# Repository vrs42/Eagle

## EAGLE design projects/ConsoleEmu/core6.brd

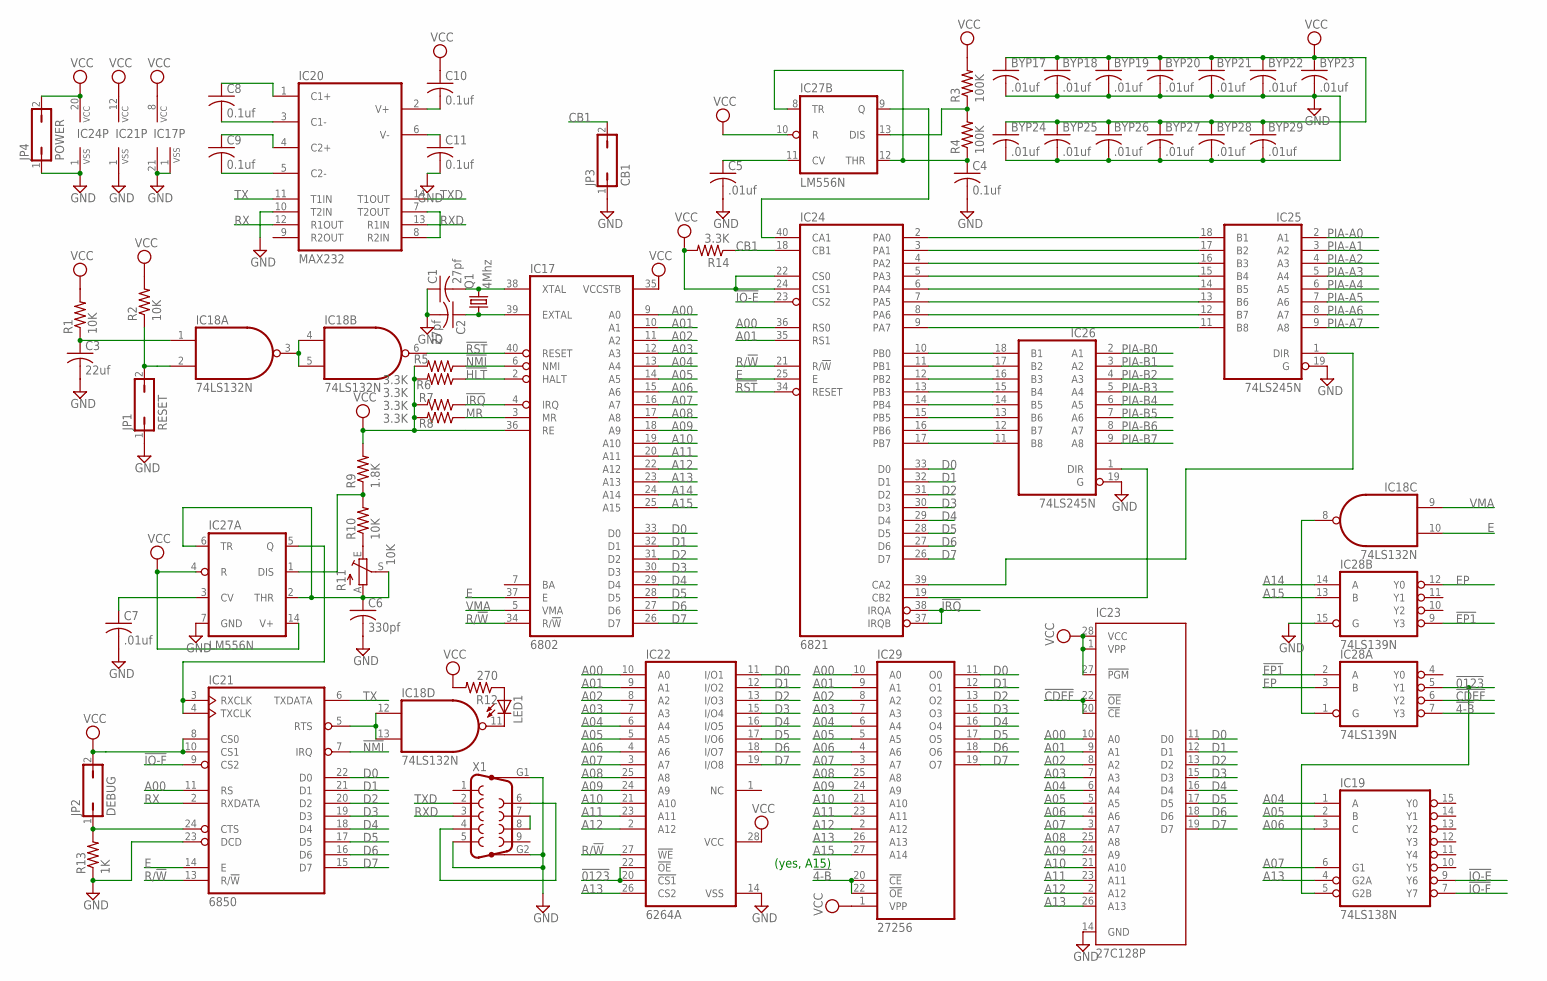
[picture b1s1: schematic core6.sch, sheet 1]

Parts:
BYP17, BYP18, BYP19, BYP20, BYP21, BYP22, BYP23, BYP24, BYP25, BYP26, BYP27, BYP28, BYP29: .01uf; C050-025X075
C1, C2: 27pf; C050-025X075
C3: 22uf; C102-043X133
C4, C8, C9, C10, C11: 0.1uf; C050-025X075
C5, C7: .01uf; C050-025X075
C6: 330pf; C050-025X075
IC17: 6802; DIL40
IC18: 74LS132N; DIL14
IC19: 74LS138N; DIL16
IC20: MAX232; DIL16
IC21: 6850; DIL24
IC22: 6264A; DIL28-6
IC23: 27C128P; DIL28-6
IC24: 6821; DIL40
IC25, IC26: 74LS245N; DIL20
IC27: LM556N; DIL14
IC28: 74LS139N; DIL16
IC29: 27256; DIL28
JP1: RESET; JP1
JP2: DEBUG; JP1
JP3: CB1; JP1
JP4: POWER; JP1
LED1: LED3MM
Q1: 4Mhz; HC18U-V
R1, R2, R10: 10K; 0207/7
R3, R4: 100K; 0207/7
R5, R6, R7, R8, R14: 3.3K; 0207/7
R9: 1.8K; 0207/7
R11: 10K; SP19L
R12: 270; 0207/7
R13: 1K; 0207/7
X1: F09HP

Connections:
!4-B: IC28.7 (Y3), IC29.20 (!CE), IC29.22 (!OE)
!0123: IC19.5 (G2B), IC22.20 (!CS1), IC22.22 (!OE), IC28.5 (Y1)
!CDEF: IC23.20 (!CE), IC23.22 (!OE), IC28.6 (Y2)
!EP1: IC28.2 (A), IC28.9 (Y3)
!HLT: IC17.2 (HALT), R5.1
!IO-E: IC19.9 (Y6), IC24.23 (CS2)
!IO-F: IC19.7 (Y7), IC21.9 (CS2)
!IRQ: IC17.4 (IRQ), IC24.37 (IRQB), IC24.38 (IRQA), R7.1
!NMI: IC17.6 (NMI), IC21.7 (IRQ), R6.1
!RST: IC17.40 (RESET), IC18.6 (O), IC24.34 (RESET)
A00: IC17.9 (A0), IC21.11 (RS), IC22.10 (A0), IC23.10 (A0), IC24.36 (RS0), IC29.10 (A0)
A01: IC17.10 (A1), IC22.9 (A1), IC23.9 (A1), IC24.35 (RS1), IC29.9 (A1)
A02: IC17.11 (A2), IC22.8 (A2), IC23.8 (A2), IC29.8 (A2)
A03: IC17.12 (A3), IC22.7 (A3), IC23.7 (A3), IC29.7 (A3)
A04: IC17.13 (A4), IC19.1 (A), IC22.6 (A4), IC23.6 (A4), IC29.6 (A4)
A05: IC17.14 (A5), IC19.2 (B), IC22.5 (A5), IC23.5 (A5), IC29.5 (A5)
A06: IC17.15 (A6), IC19.3 (C), IC22.4 (A6), IC23.4 (A6), IC29.4 (A6)
A07: IC17.16 (A7), IC19.6 (G1), IC22.3 (A7), IC23.3 (A7), IC29.3 (A7)
A08: IC17.17 (A8), IC22.25 (A8), IC23.25 (A8), IC29.25 (A8)
A09: IC17.18 (A9), IC22.24 (A9), IC23.24 (A9), IC29.24 (A9)
A10: IC17.19 (A10), IC22.21 (A10), IC23.21 (A10), IC29.21 (A10)
A11: IC17.20 (A11), IC22.23 (A11), IC23.23 (A11), IC29.23 (A11)
A12: IC17.22 (A12), IC22.2 (A12), IC23.2 (A12), IC29.2 (A12)
A13: IC17.23 (A13), IC19.4 (G2A), IC22.26 (CS2), IC23.26 (A13), IC29.26 (A13)
A14: IC17.24 (A14), IC28.14 (A)
A15: IC17.25 (A15), IC28.13 (B), IC29.27 (A14)
CB1: IC24.18 (CB1), JP3.2, R14.1
D0: IC17.33 (D0), IC21.22 (D0), IC22.11 (I/O1), IC23.11 (D0), IC24.33 (D0), IC29.11 (O0)
D1: IC17.32 (D1), IC21.21 (D1), IC22.12 (I/O2), IC23.12 (D1), IC24.32 (D1), IC29.12 (O1)
D2: IC17.31 (D2), IC21.20 (D2), IC22.13 (I/O3), IC23.13 (D2), IC24.31 (D2), IC29.13 (O2)
D3: IC17.30 (D3), IC21.19 (D3), IC22.15 (I/O4), IC23.15 (D3), IC24.30 (D3), IC29.15 (O3)
D4: IC17.29 (D4), IC21.18 (D4), IC22.16 (I/O5), IC23.16 (D4), IC24.29 (D4), IC29.16 (O4)
D5: IC17.28 (D5), IC21.17 (D5), IC22.17 (I/O6), IC23.17 (D5), IC24.28 (D5), IC29.17 (O5)
D6: IC17.27 (D6), IC21.16 (D6), IC22.18 (I/O7), IC23.18 (D6), IC24.27 (D6), IC29.18 (O6)
D7: IC17.26 (D7), IC21.15 (D7), IC22.19 (I/O8), IC23.19 (D7), IC24.26 (D7), IC29.19 (O7)
E: IC17.37 (E), IC18.10 (I1), IC21.14 (E), IC24.25 (E)
EP: IC28.3 (B), IC28.12 (Y0)
GND: BYP17.2, BYP18.2, BYP19.2, BYP20.2, BYP21.2, BYP22.2, BYP23.2, BYP24.2, BYP25.2, BYP26.2, BYP27.2, BYP28.2, BYP29.2, C1.1, C2.2, C3.2, C4.2, C5.2, C6.2, C7.2, C11.2, IC17.1 (VSS), IC17.21 (VSS), IC18.7 (GND), IC19.8 (GND), IC20.10 (T2IN), IC20.15 (GND), IC21.1 (VSS), IC21.23 (DCD), IC22.14 (VSS), IC23.14 (GND), IC24.1 (VSS), IC25.10 (GND), IC25.19 (G), IC26.10 (GND), IC26.19 (G), IC27.7 (GND), IC28.8 (GND), IC28.15 (G), IC29.14 (GND), JP1.1, JP3.1, JP4.1, R13.1, X1.5, X1.G1, X1.G2; also elsewhere on the board
MR: IC17.3 (MR), R8.1
unnamed: C2.1, IC17.39 (EXTAL), Q1.1
unnamed: C1.2, IC17.38 (XTAL), Q1.2
unnamed: IC24.2 (PA0), IC25.18 (B1)
unnamed: IC18.3 (O), IC18.4 (I0), IC18.5 (I1)
unnamed: C3.1, IC18.1 (I0), R1.1
unnamed: IC18.2 (I1), JP1.2, R2.1
unnamed: IC21.3 (RXCLK), IC21.4 (TXCLK), IC27.5 (Q)
unnamed: IC24.10 (PB0), IC26.18 (B1)
unnamed: IC24.11 (PB1), IC26.17 (B2)
unnamed: C6.1, IC27.2 (THR), IC27.6 (TR), R11.A, R11.S
unnamed: IC27.1 (DIS), R9.1, R10.2
unnamed: IC24.12 (PB2), IC26.16 (B3)
unnamed: IC24.13 (PB3), IC26.15 (B4)
unnamed: IC24.14 (PB4), IC26.14 (B5)
unnamed: IC24.15 (PB5), IC26.13 (B6)
unnamed: IC24.16 (PB6), IC26.12 (B7)
unnamed: IC24.17 (PB7), IC26.11 (B8)
unnamed: IC24.3 (PA1), IC25.17 (B2)
unnamed: IC24.4 (PA2), IC25.16 (B3)
unnamed: IC24.5 (PA3), IC25.15 (B4)
unnamed: IC24.6 (PA4), IC25.14 (B5)
unnamed: IC24.7 (PA5), IC25.13 (B6)
unnamed: IC24.8 (PA6), IC25.12 (B7)
unnamed: IC24.9 (PA7), IC25.11 (B8)
unnamed: IC24.19 (CB2), IC26.1 (DIR)
unnamed: IC24.39 (CA2), IC25.1 (DIR)
unnamed: IC24.40 (CA1), IC27.9 (Q)
unnamed: C4.1, IC27.8 (TR), IC27.12 (THR), R4.1
unnamed: IC27.13 (DIS), R3.1, R4.2
unnamed: C5.1, IC27.11 (CV)
unnamed: R10.1, R11.E
unnamed: X1.4, X1.6
unnamed: X1.7, X1.8
unnamed: IC18.12 (I0), IC18.13 (I1), IC21.5 (RTS)
unnamed: IC18.11 (O), LED1.K (C)
unnamed: LED1.A, R12.1
unnamed: IC21.24 (CTS), JP2.1, R13.2
unnamed: IC18.8 (O), IC28.1 (G)
unnamed: IC20.7 (T2OUT), IC20.8 (R2IN)
unnamed: C7.1, IC27.3 (CV)
unnamed: C9.2, IC20.5 (C2-)
unnamed: C9.1, IC20.4 (C2+)
unnamed: C8.2, IC20.3 (C1-)
unnamed: C8.1, IC20.1 (C1+)
unnamed: C11.1, IC20.6 (V-)
unnamed: C10.2, IC20.2 (V+)
PIA-A0: IC25.2 (A1); also elsewhere on the board
PIA-A1: IC25.3 (A2); also elsewhere on the board
PIA-A2: IC25.4 (A3); also elsewhere on the board
PIA-A3: IC25.5 (A4); also elsewhere on the board
PIA-A4: IC25.6 (A5); also elsewhere on the board
PIA-A5: IC25.7 (A6); also elsewhere on the board
PIA-A6: IC25.8 (A7); also elsewhere on the board
PIA-A7: IC25.9 (A8); also elsewhere on the board
PIA-B0: IC26.2 (A1); also elsewhere on the board
PIA-B1: IC26.3 (A2); also elsewhere on the board
PIA-B2: IC26.4 (A3); also elsewhere on the board
PIA-B3: IC26.5 (A4); also elsewhere on the board
PIA-B4: IC26.6 (A5); also elsewhere on the board
PIA-B5: IC26.7 (A6); also elsewhere on the board
PIA-B6: IC26.8 (A7); also elsewhere on the board
PIA-B7: IC26.9 (A8); also elsewhere on the board
R/!W: IC17.34 (R/!W), IC21.13 (R/!W), IC22.27 (!WE), IC24.21 (R/!W)
RX: IC20.12 (R1OUT), IC21.2 (RXDATA)
RXD: IC20.13 (R1IN), X1.3
TX: IC20.11 (T1IN), IC21.6 (TXDATA)
TXD: IC20.14 (T1OUT), X1.2
VCC: BYP17.1, BYP18.1, BYP19.1, BYP20.1, BYP21.1, BYP22.1, BYP23.1, BYP24.1, BYP25.1, BYP26.1, BYP27.1, BYP28.1, BYP29.1, C10.1, IC17.8 (VCC), IC17.35 (VCCSTB), IC17.36 (RE), IC18.14 (VCC), IC19.16 (VCC), IC20.16 (VCC), IC21.8 (CS0), IC21.10 (CS1), IC21.12 (VCC), IC22.28 (VCC), IC23.1 (VPP), IC23.27 (!PGM), IC23.28 (VCC), IC24.20 (VCC), IC24.22 (CS0), IC24.24 (CS1), IC25.20 (VCC), IC26.20 (VCC), IC27.4 (R), IC27.10 (R), IC27.14 (V+), IC28.16 (VCC), IC29.1 (VPP), IC29.28 (VCC), JP2.2, JP4.2, R1.2, R2.2, R3.2, R5.2, R6.2, R7.2, R8.2, R9.2, R12.2, R14.2; also elsewhere on the board
VMA: IC17.5 (VMA), IC18.9 (I0)

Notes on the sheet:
(yes, A15)

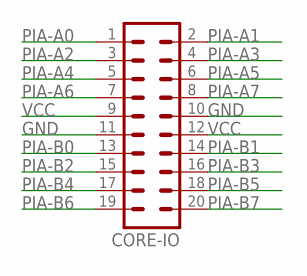
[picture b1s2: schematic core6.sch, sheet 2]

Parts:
CORE-IO: MA10-2

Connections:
GND: CORE-IO.10, CORE-IO.11; also elsewhere on the board
PIA-A0: CORE-IO.1; also elsewhere on the board
PIA-A1: CORE-IO.2; also elsewhere on the board
PIA-A2: CORE-IO.3; also elsewhere on the board
PIA-A3: CORE-IO.4; also elsewhere on the board
PIA-A4: CORE-IO.5; also elsewhere on the board
PIA-A5: CORE-IO.6; also elsewhere on the board
PIA-A6: CORE-IO.7; also elsewhere on the board
PIA-A7: CORE-IO.8; also elsewhere on the board
PIA-B0: CORE-IO.13; also elsewhere on the board
PIA-B1: CORE-IO.14; also elsewhere on the board
PIA-B2: CORE-IO.15; also elsewhere on the board
PIA-B3: CORE-IO.16; also elsewhere on the board
PIA-B4: CORE-IO.17; also elsewhere on the board
PIA-B5: CORE-IO.18; also elsewhere on the board
PIA-B6: CORE-IO.19; also elsewhere on the board
PIA-B7: CORE-IO.20; also elsewhere on the board
VCC: CORE-IO.9, CORE-IO.12; also elsewhere on the board

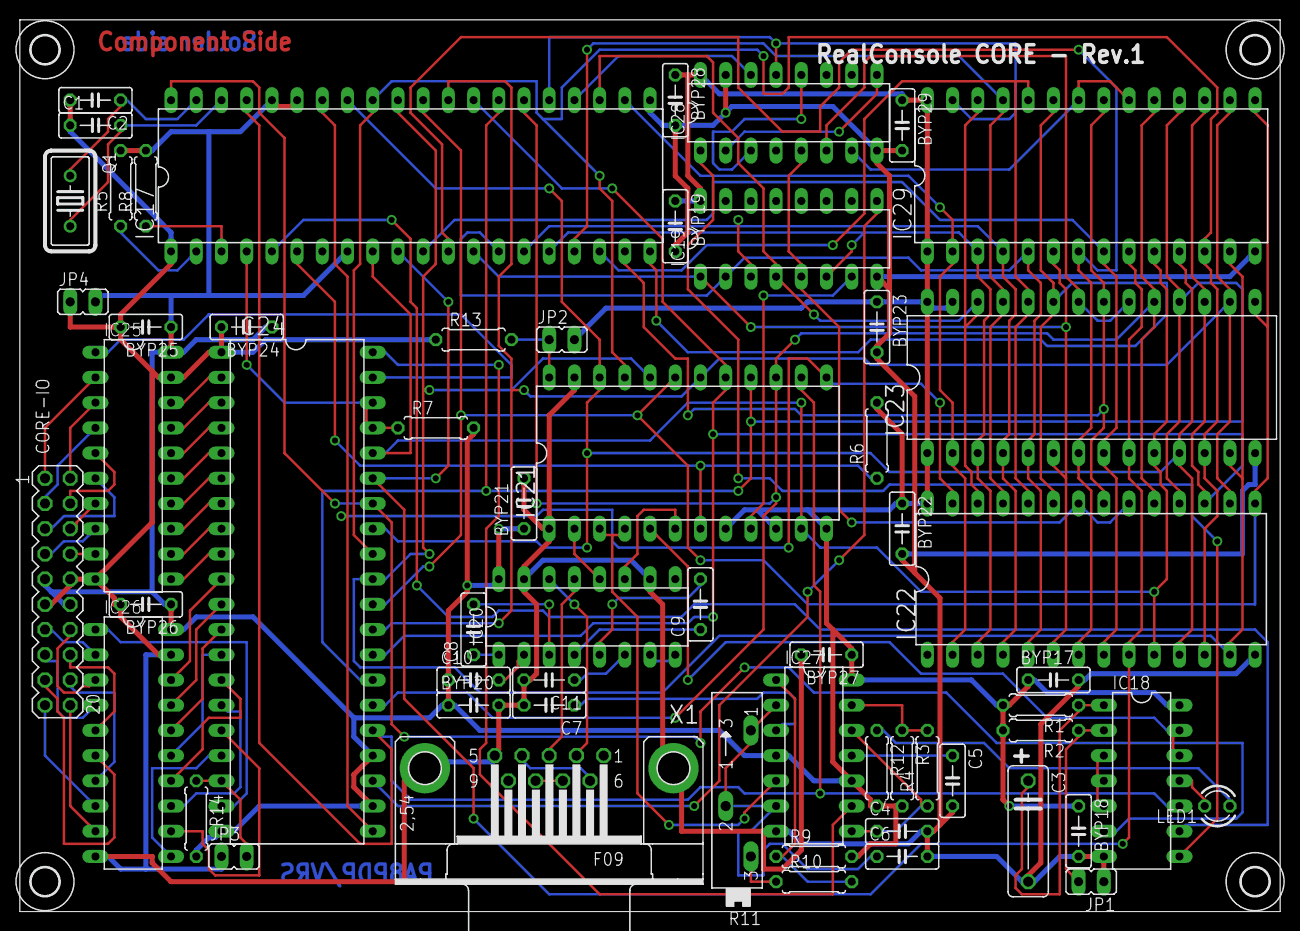
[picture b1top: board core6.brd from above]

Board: 2 copper layers, 127.0 x 89.8 mm, 63 parts (0 on the bottom side), 108 nets.

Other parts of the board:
U$3, U$4, U$5, U$6: 2,8

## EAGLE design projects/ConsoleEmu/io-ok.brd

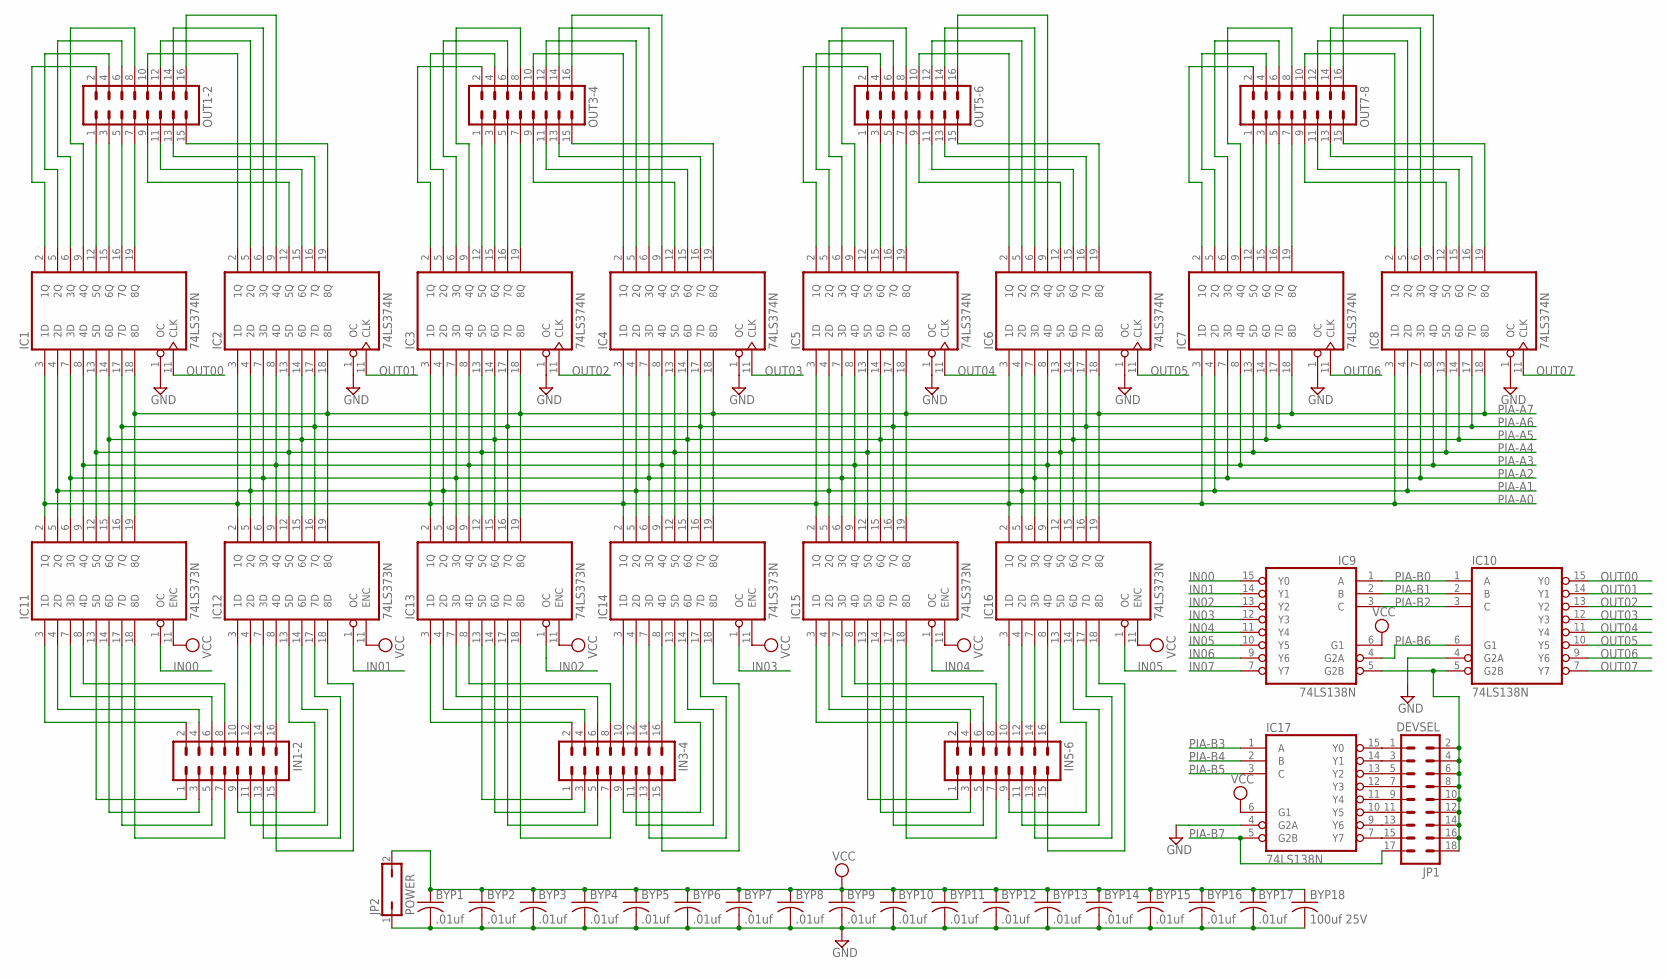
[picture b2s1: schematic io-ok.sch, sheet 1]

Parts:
BYP1, BYP2, BYP3, BYP4, BYP5, BYP6, BYP7, BYP8, BYP9, BYP10, BYP11, BYP12, BYP13, BYP14, BYP15, BYP16, BYP17: .01uf; C050-025X075
BYP18: 100uf 25V; C150-064X183
IC1, IC2, IC3, IC4, IC5, IC6, IC7, IC8: 74LS374N; DIL20
IC9, IC10, IC17: 74LS138N; DIL16
IC11, IC12, IC13, IC14, IC15, IC16: 74LS373N; DIL20
IN1-2, IN3-4, IN5-6: MA08-2
JP1: DEVSEL; MA09-2
JP2: POWER; JP1
OUT1-2, OUT3-4, OUT5-6, OUT7-8: MA08-2

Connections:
GND: BYP1.2, BYP2.2, BYP3.2, BYP4.2, BYP5.2, BYP6.2, BYP7.2, BYP8.2, BYP9.2, BYP10.2, BYP11.2, BYP12.2, BYP13.2, BYP14.2, BYP15.2, BYP16.2, BYP17.2, BYP18.2, IC1.1 (OC), IC1.10 (GND), IC2.1 (OC), IC2.10 (GND), IC3.1 (OC), IC3.10 (GND), IC4.1 (OC), IC4.10 (GND), IC5.1 (OC), IC5.10 (GND), IC6.1 (OC), IC6.10 (GND), IC7.1 (OC), IC7.10 (GND), IC8.1 (OC), IC8.10 (GND), IC9.8 (GND), IC10.4 (G2A), IC10.8 (GND), IC11.10 (GND), IC12.10 (GND), IC13.10 (GND), IC14.10 (GND), IC15.10 (GND), IC16.10 (GND), IC17.4 (G2A), IC17.8 (GND), JP2.1; also elsewhere on the board
IN00: IC9.15 (Y0), IC11.1 (OC)
IN01: IC9.14 (Y1), IC12.1 (OC)
IN02: IC9.13 (Y2), IC13.1 (OC)
IN03: IC9.12 (Y3), IC14.1 (OC)
IN04: IC9.11 (Y4), IC15.1 (OC)
IN05: IC9.10 (Y5), IC16.1 (OC)
IN06: IC9.9 (Y6)
IN07: IC9.7 (Y7)
unnamed: IC12.3 (1D), IN1-2.10
unnamed: IC12.4 (2D), IN1-2.12
unnamed: IC17.15 (Y0), JP1.1
unnamed: IC17.14 (Y1), JP1.3
unnamed: IC17.13 (Y2), JP1.5
unnamed: IC17.12 (Y3), JP1.7
unnamed: IC12.7 (3D), IN1-2.14
unnamed: IC12.8 (4D), IN1-2.16
unnamed: IC11.8 (4D), IN1-2.8
unnamed: IC11.7 (3D), IN1-2.6
unnamed: IC11.4 (2D), IN1-2.4
unnamed: IC11.3 (1D), IN1-2.2
unnamed: IC11.13 (5D), IN1-2.1
unnamed: IC11.14 (6D), IN1-2.3
unnamed: IC11.17 (7D), IN1-2.5
unnamed: IC11.18 (8D), IN1-2.7
unnamed: IC12.13 (5D), IN1-2.9
unnamed: IC12.14 (6D), IN1-2.11
unnamed: IC12.17 (7D), IN1-2.13
unnamed: IC12.18 (8D), IN1-2.15
unnamed: IC17.11 (Y4), JP1.9
unnamed: IC17.10 (Y5), JP1.11
unnamed: IC17.9 (Y6), JP1.13
unnamed: IC17.7 (Y7), JP1.15
unnamed: IC9.5 (G2B), IC10.5 (G2B), JP1.2, JP1.4, JP1.6, JP1.8, JP1.10, JP1.12, JP1.14, JP1.16, JP1.18
unnamed: IC5.2 (1Q), OUT5-6.2
unnamed: IC7.2 (1Q), OUT7-8.2
unnamed: IC14.3 (1D), IN3-4.10
unnamed: IC14.4 (2D), IN3-4.12
unnamed: IC14.7 (3D), IN3-4.14
unnamed: IC14.8 (4D), IN3-4.16
unnamed: IC3.12 (5Q), OUT3-4.1
unnamed: IC3.15 (6Q), OUT3-4.3
unnamed: IC3.16 (7Q), OUT3-4.5
unnamed: IC3.19 (8Q), OUT3-4.7
unnamed: IC13.3 (1D), IN3-4.2
unnamed: IC13.4 (2D), IN3-4.4
unnamed: IC13.7 (3D), IN3-4.6
unnamed: IC13.8 (4D), IN3-4.8
unnamed: IC14.13 (5D), IN3-4.9
unnamed: IC14.14 (6D), IN3-4.11
unnamed: IC14.17 (7D), IN3-4.13
unnamed: IC14.18 (8D), IN3-4.15
unnamed: IC13.13 (5D), IN3-4.1
unnamed: IC13.14 (6D), IN3-4.3
unnamed: IC13.17 (7D), IN3-4.5
unnamed: IC13.18 (8D), IN3-4.7
unnamed: IC3.5 (2Q), OUT3-4.4
unnamed: IC3.6 (3Q), OUT3-4.6
unnamed: IC3.2 (1Q), OUT3-4.2
unnamed: IC3.9 (4Q), OUT3-4.8
unnamed: IC1.12 (5Q), OUT1-2.1
unnamed: IC1.15 (6Q), OUT1-2.3
unnamed: IC1.16 (7Q), OUT1-2.5
unnamed: IC1.19 (8Q), OUT1-2.7
unnamed: IC1.2 (1Q), OUT1-2.2
unnamed: IC1.5 (2Q), OUT1-2.4
unnamed: IC1.6 (3Q), OUT1-2.6
unnamed: IC1.9 (4Q), OUT1-2.8
unnamed: IC2.19 (8Q), OUT1-2.15
unnamed: IC2.16 (7Q), OUT1-2.13
unnamed: IC2.15 (6Q), OUT1-2.11
unnamed: IC2.12 (5Q), OUT1-2.9
unnamed: IC2.2 (1Q), OUT1-2.10
unnamed: IC2.5 (2Q), OUT1-2.12
unnamed: IC2.6 (3Q), OUT1-2.14
unnamed: IC2.9 (4Q), OUT1-2.16
unnamed: IC4.2 (1Q), OUT3-4.10
unnamed: IC4.5 (2Q), OUT3-4.12
unnamed: IC4.6 (3Q), OUT3-4.14
unnamed: IC4.9 (4Q), OUT3-4.16
unnamed: IC4.19 (8Q), OUT3-4.15
unnamed: IC4.16 (7Q), OUT3-4.13
unnamed: IC4.15 (6Q), OUT3-4.11
unnamed: IC4.12 (5Q), OUT3-4.9
unnamed: IC16.3 (1D), IN5-6.10
unnamed: IC16.4 (2D), IN5-6.12
unnamed: IC16.7 (3D), IN5-6.14
unnamed: IC16.8 (4D), IN5-6.16
unnamed: IC5.12 (5Q), OUT5-6.1
unnamed: IC5.15 (6Q), OUT5-6.3
unnamed: IC5.16 (7Q), OUT5-6.5
unnamed: IC5.19 (8Q), OUT5-6.7
unnamed: IC7.12 (5Q), OUT7-8.1
unnamed: IC7.15 (6Q), OUT7-8.3
unnamed: IC7.16 (7Q), OUT7-8.5
unnamed: IC7.19 (8Q), OUT7-8.7
unnamed: IC5.5 (2Q), OUT5-6.4
unnamed: IC5.6 (3Q), OUT5-6.6
unnamed: IC5.9 (4Q), OUT5-6.8
unnamed: IC6.12 (5Q), OUT5-6.9
unnamed: IC6.15 (6Q), OUT5-6.11
unnamed: IC6.16 (7Q), OUT5-6.13
unnamed: IC6.19 (8Q), OUT5-6.15
unnamed: IC6.2 (1Q), OUT5-6.10
unnamed: IC6.5 (2Q), OUT5-6.12
unnamed: IC6.6 (3Q), OUT5-6.14
unnamed: IC6.9 (4Q), OUT5-6.16
unnamed: IC15.3 (1D), IN5-6.2
unnamed: IC15.4 (2D), IN5-6.4
unnamed: IC15.7 (3D), IN5-6.6
unnamed: IC15.8 (4D), IN5-6.8
unnamed: IC16.13 (5D), IN5-6.9
unnamed: IC16.14 (6D), IN5-6.11
unnamed: IC16.17 (7D), IN5-6.13
unnamed: IC16.18 (8D), IN5-6.15
unnamed: IC15.13 (5D), IN5-6.1
unnamed: IC15.14 (6D), IN5-6.3
unnamed: IC15.17 (7D), IN5-6.5
unnamed: IC15.18 (8D), IN5-6.7
unnamed: IC8.19 (8Q), OUT7-8.15
unnamed: IC8.16 (7Q), OUT7-8.13
unnamed: IC8.15 (6Q), OUT7-8.11
unnamed: IC8.12 (5Q), OUT7-8.9
unnamed: IC8.2 (1Q), OUT7-8.10
unnamed: IC8.5 (2Q), OUT7-8.12
unnamed: IC8.6 (3Q), OUT7-8.14
unnamed: IC8.9 (4Q), OUT7-8.16
unnamed: IC7.9 (4Q), OUT7-8.8
unnamed: IC7.6 (3Q), OUT7-8.6
unnamed: IC7.5 (2Q), OUT7-8.4
OUT00: IC1.11 (CLK), IC10.15 (Y0)
OUT01: IC2.11 (CLK), IC10.14 (Y1)
OUT02: IC3.11 (CLK), IC10.13 (Y2)
OUT03: IC4.11 (CLK), IC10.12 (Y3)
OUT04: IC5.11 (CLK), IC10.11 (Y4)
OUT05: IC6.11 (CLK), IC10.10 (Y5)
OUT06: IC7.11 (CLK), IC10.9 (Y6)
OUT07: IC8.11 (CLK), IC10.7 (Y7)
PIA-A0: IC1.3 (1D), IC2.3 (1D), IC3.3 (1D), IC4.3 (1D), IC5.3 (1D), IC6.3 (1D), IC7.3 (1D), IC8.3 (1D), IC11.2 (1Q), IC12.2 (1Q), IC13.2 (1Q), IC14.2 (1Q), IC15.2 (1Q), IC16.2 (1Q); also elsewhere on the board
PIA-A1: IC1.4 (2D), IC2.4 (2D), IC3.4 (2D), IC4.4 (2D), IC5.4 (2D), IC6.4 (2D), IC7.4 (2D), IC8.4 (2D), IC11.5 (2Q), IC12.5 (2Q), IC13.5 (2Q), IC14.5 (2Q), IC15.5 (2Q), IC16.5 (2Q); also elsewhere on the board
PIA-A2: IC1.7 (3D), IC2.7 (3D), IC3.7 (3D), IC4.7 (3D), IC5.7 (3D), IC6.7 (3D), IC7.7 (3D), IC8.7 (3D), IC11.6 (3Q), IC12.6 (3Q), IC13.6 (3Q), IC14.6 (3Q), IC15.6 (3Q), IC16.6 (3Q); also elsewhere on the board
PIA-A3: IC1.8 (4D), IC2.8 (4D), IC3.8 (4D), IC4.8 (4D), IC5.8 (4D), IC6.8 (4D), IC7.8 (4D), IC8.8 (4D), IC11.9 (4Q), IC12.9 (4Q), IC13.9 (4Q), IC14.9 (4Q), IC15.9 (4Q), IC16.9 (4Q); also elsewhere on the board
PIA-A4: IC1.13 (5D), IC2.13 (5D), IC3.13 (5D), IC4.13 (5D), IC5.13 (5D), IC6.13 (5D), IC7.13 (5D), IC8.13 (5D), IC11.12 (5Q), IC12.12 (5Q), IC13.12 (5Q), IC14.12 (5Q), IC15.12 (5Q), IC16.12 (5Q); also elsewhere on the board
PIA-A5: IC1.14 (6D), IC2.14 (6D), IC3.14 (6D), IC4.14 (6D), IC5.14 (6D), IC6.14 (6D), IC7.14 (6D), IC8.14 (6D), IC11.15 (6Q), IC12.15 (6Q), IC13.15 (6Q), IC14.15 (6Q), IC15.15 (6Q), IC16.15 (6Q); also elsewhere on the board
PIA-A6: IC1.17 (7D), IC2.17 (7D), IC3.17 (7D), IC4.17 (7D), IC5.17 (7D), IC6.17 (7D), IC7.17 (7D), IC8.17 (7D), IC11.16 (7Q), IC12.16 (7Q), IC13.16 (7Q), IC14.16 (7Q), IC15.16 (7Q), IC16.16 (7Q); also elsewhere on the board
PIA-A7: IC1.18 (8D), IC2.18 (8D), IC3.18 (8D), IC4.18 (8D), IC5.18 (8D), IC6.18 (8D), IC7.18 (8D), IC8.18 (8D), IC11.19 (8Q), IC12.19 (8Q), IC13.19 (8Q), IC14.19 (8Q), IC15.19 (8Q), IC16.19 (8Q); also elsewhere on the board
PIA-B0: IC9.1 (A), IC10.1 (A); also elsewhere on the board
PIA-B1: IC9.2 (B), IC10.2 (B); also elsewhere on the board
PIA-B2: IC9.3 (C), IC10.3 (C); also elsewhere on the board
PIA-B3: IC17.1 (A); also elsewhere on the board
PIA-B4: IC17.2 (B); also elsewhere on the board
PIA-B5: IC17.3 (C); also elsewhere on the board
PIA-B6: IC9.4 (G2A), IC10.6 (G1); also elsewhere on the board
PIA-B7: IC17.5 (G2B), JP1.17; also elsewhere on the board
VCC: BYP1.1, BYP2.1, BYP3.1, BYP4.1, BYP5.1, BYP6.1, BYP7.1, BYP8.1, BYP9.1, BYP10.1, BYP11.1, BYP12.1, BYP13.1, BYP14.1, BYP15.1, BYP16.1, BYP17.1, BYP18.1, IC1.20 (VCC), IC2.20 (VCC), IC3.20 (VCC), IC4.20 (VCC), IC5.20 (VCC), IC6.20 (VCC), IC7.20 (VCC), IC8.20 (VCC), IC9.6 (G1), IC9.16 (VCC), IC10.16 (VCC), IC11.11 (ENC), IC11.20 (VCC), IC12.11 (ENC), IC12.20 (VCC), IC13.11 (ENC), IC13.20 (VCC), IC14.11 (ENC), IC14.20 (VCC), IC15.11 (ENC), IC15.20 (VCC), IC16.11 (ENC), IC16.20 (VCC), IC17.6 (G1), IC17.16 (VCC), JP2.2; also elsewhere on the board

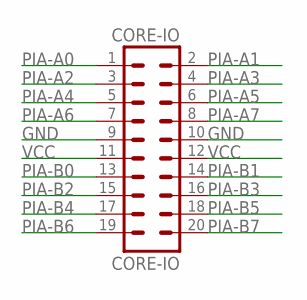
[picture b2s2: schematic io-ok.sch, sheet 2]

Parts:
CORE-IO: CORE-IO; MA10-2

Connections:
GND: CORE-IO.9, CORE-IO.10; also elsewhere on the board
PIA-A0: CORE-IO.1; also elsewhere on the board
PIA-A1: CORE-IO.2; also elsewhere on the board
PIA-A2: CORE-IO.3; also elsewhere on the board
PIA-A3: CORE-IO.4; also elsewhere on the board
PIA-A4: CORE-IO.5; also elsewhere on the board
PIA-A5: CORE-IO.6; also elsewhere on the board
PIA-A6: CORE-IO.7; also elsewhere on the board
PIA-A7: CORE-IO.8; also elsewhere on the board
PIA-B0: CORE-IO.13; also elsewhere on the board
PIA-B1: CORE-IO.14; also elsewhere on the board
PIA-B2: CORE-IO.15; also elsewhere on the board
PIA-B3: CORE-IO.16; also elsewhere on the board
PIA-B4: CORE-IO.17; also elsewhere on the board
PIA-B5: CORE-IO.18; also elsewhere on the board
PIA-B6: CORE-IO.19; also elsewhere on the board
PIA-B7: CORE-IO.20; also elsewhere on the board
VCC: CORE-IO.11, CORE-IO.12; also elsewhere on the board

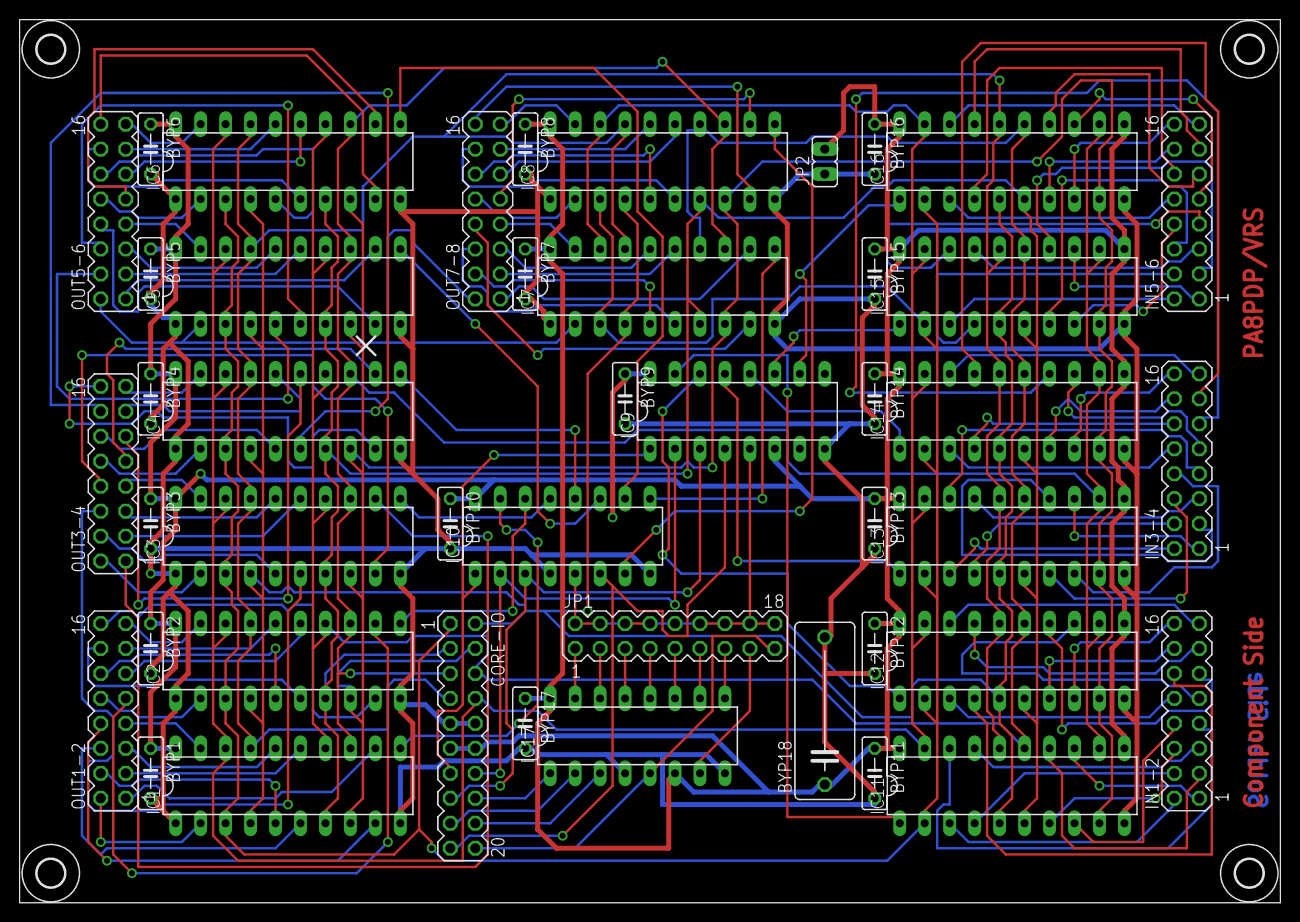
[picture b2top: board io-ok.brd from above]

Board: 2 copper layers, 128.2 x 89.8 mm, 49 parts (0 on the bottom side), 153 nets.

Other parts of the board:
U$1, U$2, U$3, U$4: 2,8
